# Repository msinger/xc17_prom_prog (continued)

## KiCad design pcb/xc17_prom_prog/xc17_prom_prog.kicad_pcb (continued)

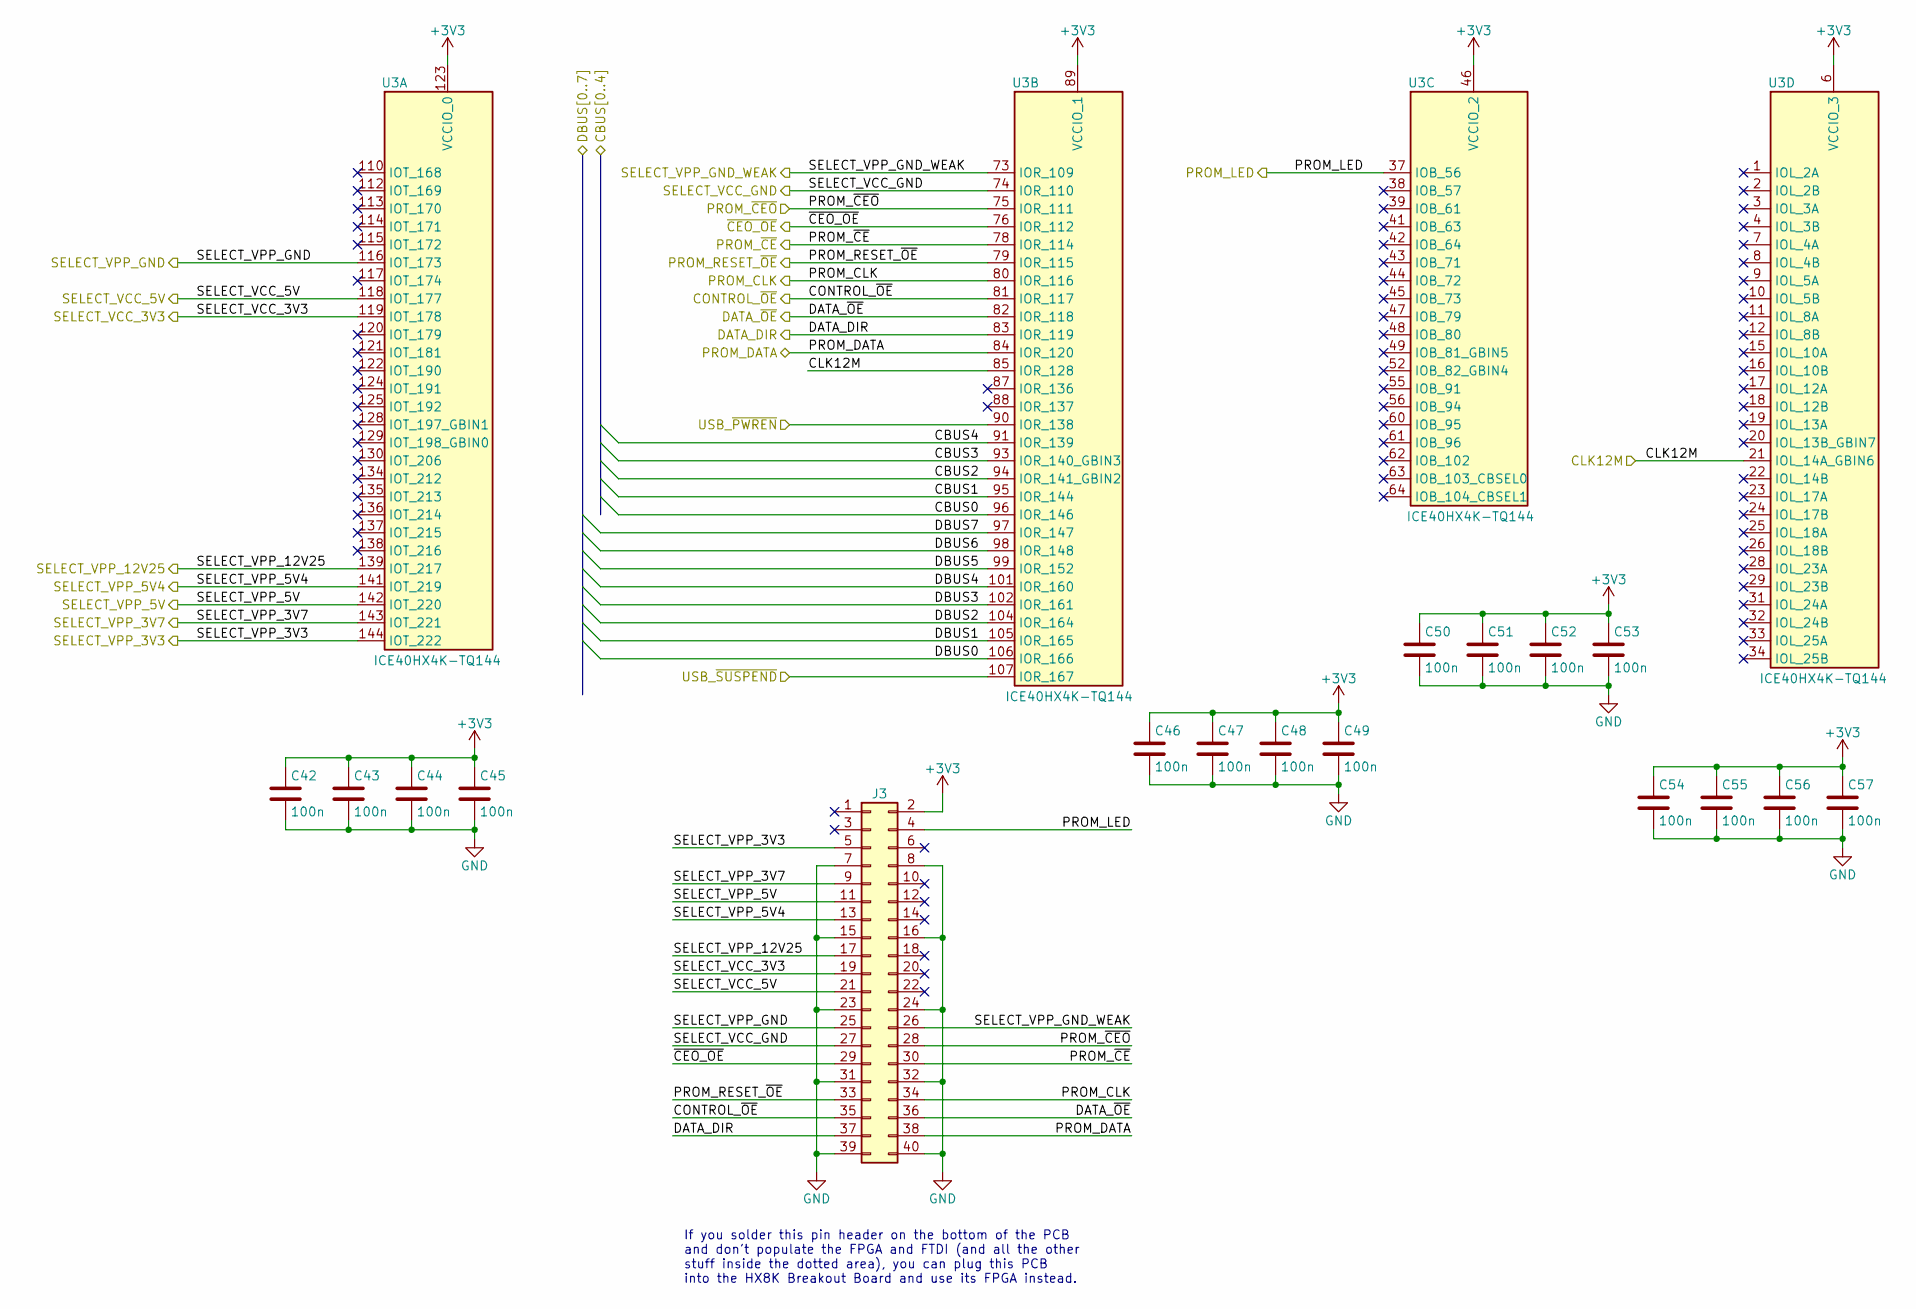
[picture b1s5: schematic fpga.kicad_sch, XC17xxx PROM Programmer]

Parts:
C42, C43, C44, C45, C46, C47, C48, C49, C50, C51, C52, C53, C54, C55, C56, C57: 100n; C_0603_1608Metric
J3: Conn_02x20_Odd_Even; PinHeader_2x20_P2.54mm_Vertical
U3: ICE40HX4K-TQ144; TQFP-144_20x20mm_P0.5mm

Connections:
+3V3: C42.1, C43.1, C44.1, C45.1, C46.1, C47.1, C48.1, C49.1, C50.1, C51.1, C52.1, C53.1, C54.1, C55.1, C56.1, C57.1, J3.2, U3.6 (VCCIO_3), U3.30 (VCCIO_3), U3.46 (VCCIO_2), U3.57 (VCCIO_2), U3.89 (VCCIO_1), U3.100 (VCCIO_1), U3.123 (VCCIO_0), U3.131 (VCCIO_0); also elsewhere on the board
/FPGA Power/CBUS0: U3.96 (IOR_146); also elsewhere on the board
/FPGA Power/CBUS1: U3.95 (IOR_144); also elsewhere on the board
/FPGA Power/CBUS2: U3.94 (IOR_141_GBIN2); also elsewhere on the board
/FPGA Power/CBUS3: U3.93 (IOR_140_GBIN3); also elsewhere on the board
/FPGA Power/CBUS4: U3.91 (IOR_139); also elsewhere on the board
/FPGA Power/DBUS0: U3.106 (IOR_166); also elsewhere on the board
/FPGA Power/DBUS1: U3.105 (IOR_165); also elsewhere on the board
/FPGA Power/DBUS2: U3.104 (IOR_164); also elsewhere on the board
/FPGA Power/DBUS3: U3.102 (IOR_161); also elsewhere on the board
/FPGA Power/DBUS4: U3.101 (IOR_160); also elsewhere on the board
/FPGA Power/DBUS5: U3.99 (IOR_152); also elsewhere on the board
/FPGA Power/DBUS6: U3.98 (IOR_148); also elsewhere on the board
/FPGA Power/DBUS7: U3.97 (IOR_147); also elsewhere on the board
/FPGA Power/USB_~PWREN: U3.90 (IOR_138); also elsewhere on the board
/FPGA Power/USB_~SUSPEND: U3.107 (IOR_167); also elsewhere on the board
/FPGA/CLK12M: U3.21 (IOL_14A_GBIN6), U3.85 (IOR_128); also elsewhere on the board
/FPGA/CONTROL_~OE: J3.35, U3.81 (IOR_117); also elsewhere on the board
/FPGA/DATA_DIR: J3.37, U3.83 (IOR_119); also elsewhere on the board
/FPGA/DATA_~OE: J3.36, U3.82 (IOR_118); also elsewhere on the board
/FPGA/PROM_CLK: J3.34, U3.80 (IOR_116); also elsewhere on the board
/FPGA/PROM_DATA: J3.38, U3.84 (IOR_120); also elsewhere on the board
/FPGA/PROM_LED: J3.4, U3.37 (IOB_56); also elsewhere on the board
/FPGA/PROM_RESET_~OE: J3.33, U3.79 (IOR_115); also elsewhere on the board
/FPGA/PROM_~CEO: J3.28, U3.75 (IOR_111); also elsewhere on the board
/FPGA/PROM_~CE: J3.30, U3.78 (IOR_114); also elsewhere on the board
/FPGA/SELECT_VCC_3V3: J3.19, U3.119 (IOT_178); also elsewhere on the board
/FPGA/SELECT_VCC_5V: J3.21, U3.118 (IOT_177); also elsewhere on the board
/FPGA/SELECT_VCC_GND: J3.27, U3.74 (IOR_110); also elsewhere on the board
/FPGA/SELECT_VPP_3V3: J3.5, U3.144 (IOT_222); also elsewhere on the board
/FPGA/SELECT_VPP_3V7: J3.9, U3.143 (IOT_221); also elsewhere on the board
/FPGA/SELECT_VPP_5V: J3.11, U3.142 (IOT_220); also elsewhere on the board
/FPGA/SELECT_VPP_5V4: J3.13, U3.141 (IOT_219); also elsewhere on the board
/FPGA/SELECT_VPP_12V25: J3.17, U3.139 (IOT_217); also elsewhere on the board
/FPGA/SELECT_VPP_GND: J3.25, U3.116 (IOT_173); also elsewhere on the board
/FPGA/SELECT_VPP_GND_WEAK: J3.26, U3.73 (IOR_109); also elsewhere on the board
/FPGA/~CEO_OE: J3.29, U3.76 (IOR_112); also elsewhere on the board
GND: C42.2, C43.2, C44.2, C45.2, C46.2, C47.2, C48.2, C49.2, C50.2, C51.2, C52.2, C53.2, C54.2, C55.2, C56.2, C57.2, J3.7, J3.8, J3.15, J3.16, J3.23, J3.24, J3.31, J3.32, J3.39, J3.40; also elsewhere on the board

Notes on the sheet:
If you solder this pin header on the bottom of the PCB and don't populate the FPGA and FTDI (and all the other stuff inside the dotted area), you can plug this PCB into the HX8K Breakout Board and use its FPGA instead.

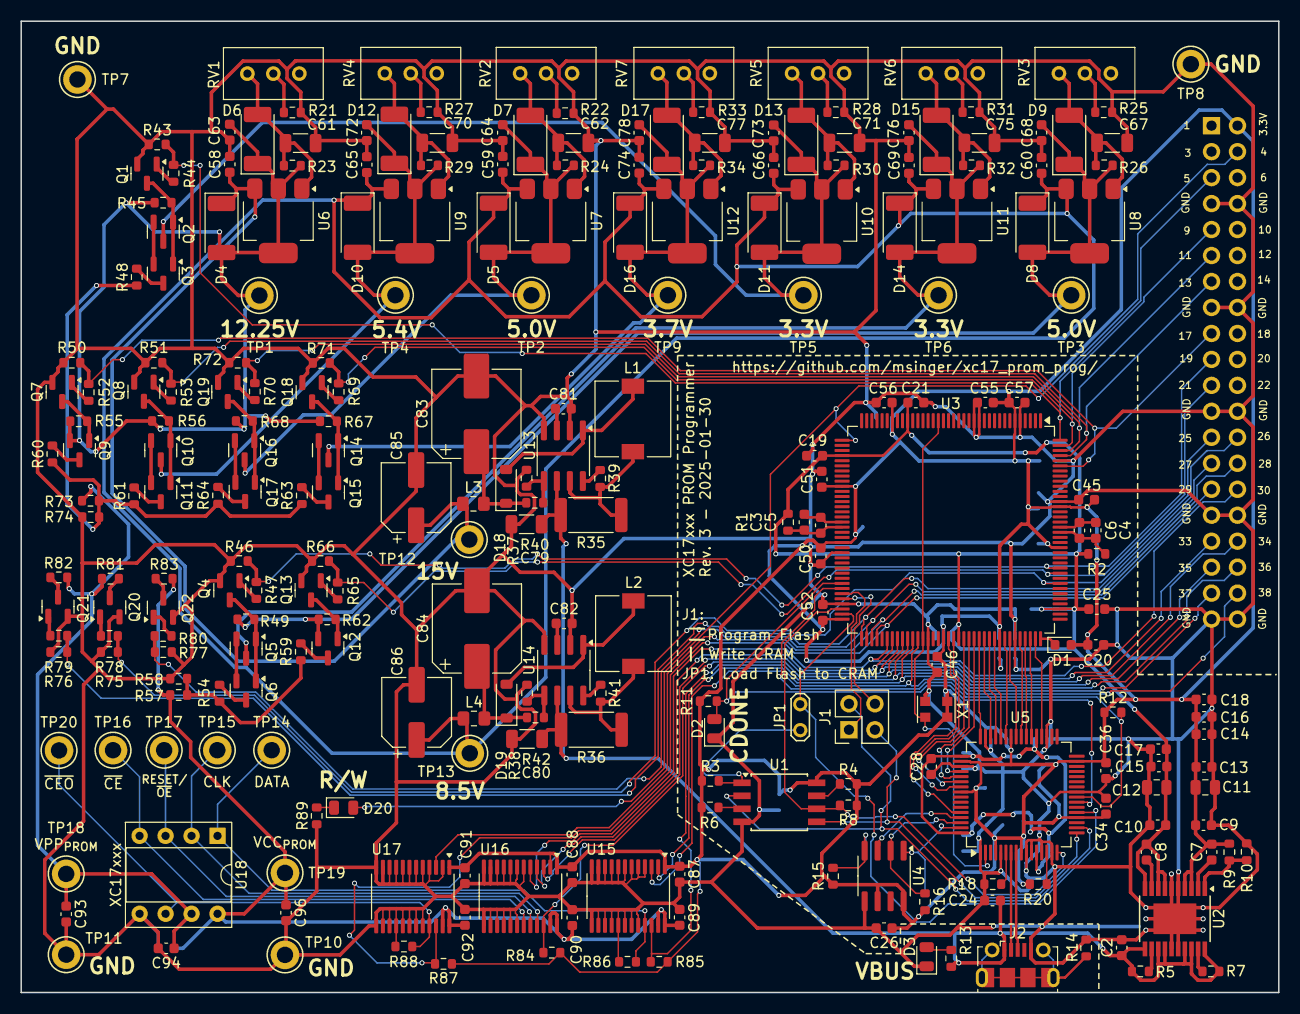
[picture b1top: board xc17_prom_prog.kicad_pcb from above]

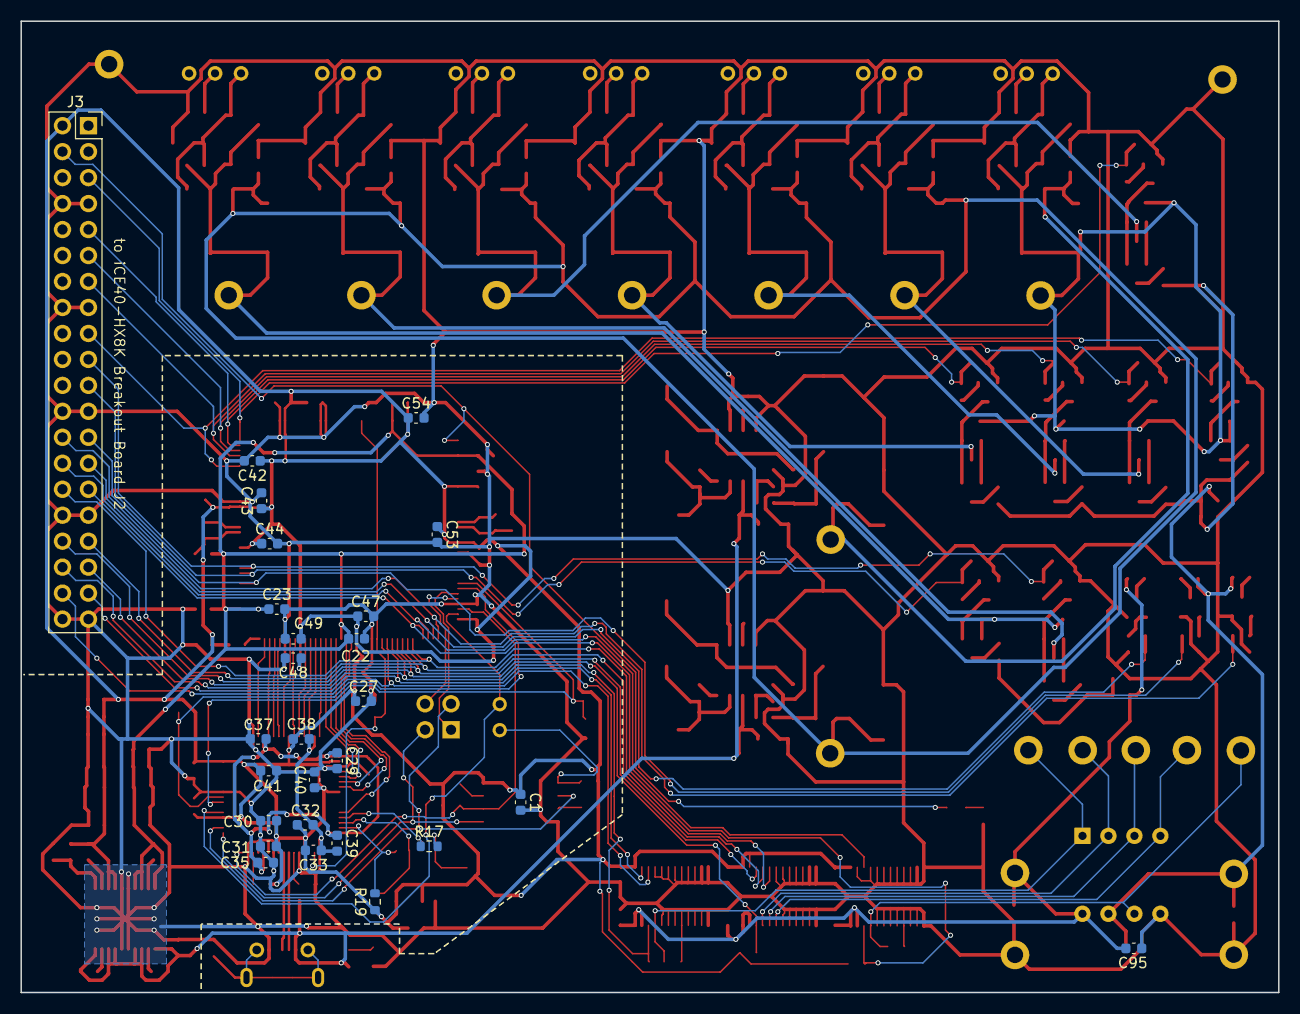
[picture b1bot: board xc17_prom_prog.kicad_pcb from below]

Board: 2 copper layers, 123.0 x 95.0 mm, 281 parts (26 on the bottom side), 149 nets.

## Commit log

2024-11-29 Fix MOSFETs
    * Block MOSFET body diodes by placing two MOSFETs in anti series.
    * Connect PROM LED to pin header.
    * Add transistors to actively pull PROM VCC and VPP low.
2024-12-05 initial Verilog and C# code
    * Capable of reading Maufacturer and Device ID from PROM.
2024-12-08 Implement more precise voltage controls
2024-12-08 Add FTDI configuration template
2024-12-08 Fix pin numbers in code for new PCB rev
2024-12-29 Fix voltage over-/under-shots
2025-01-10 Implement read chip and read reset polarity
2025-01-11 Implement blank check
2025-01-12 Implement verify
2025-01-29 Implement actual programming
    Bitstream is too big for the HX1K FPGA. Needed to use the HX8K Breakout
    Board. Will change the PCB to host an HX4K FPGA later.
    I successfully programmed my first XC17S20XL PROM chip with this commit!
    Reset polarity is not yet done.
2025-01-29 Implement programming reset polarity
2025-01-29 Remove unused components
2025-01-30 Migrate from HX1K to HX4K FPGA
2025-01-31 Document calibration and testing in README.md
2025-01-31 Document usage in README.md
2025-02-16 Update README.md with pictures
2025-03-29 Ignore *.kicad_prl
2025-04-16 Fix for Fedora 42 C# compiler
